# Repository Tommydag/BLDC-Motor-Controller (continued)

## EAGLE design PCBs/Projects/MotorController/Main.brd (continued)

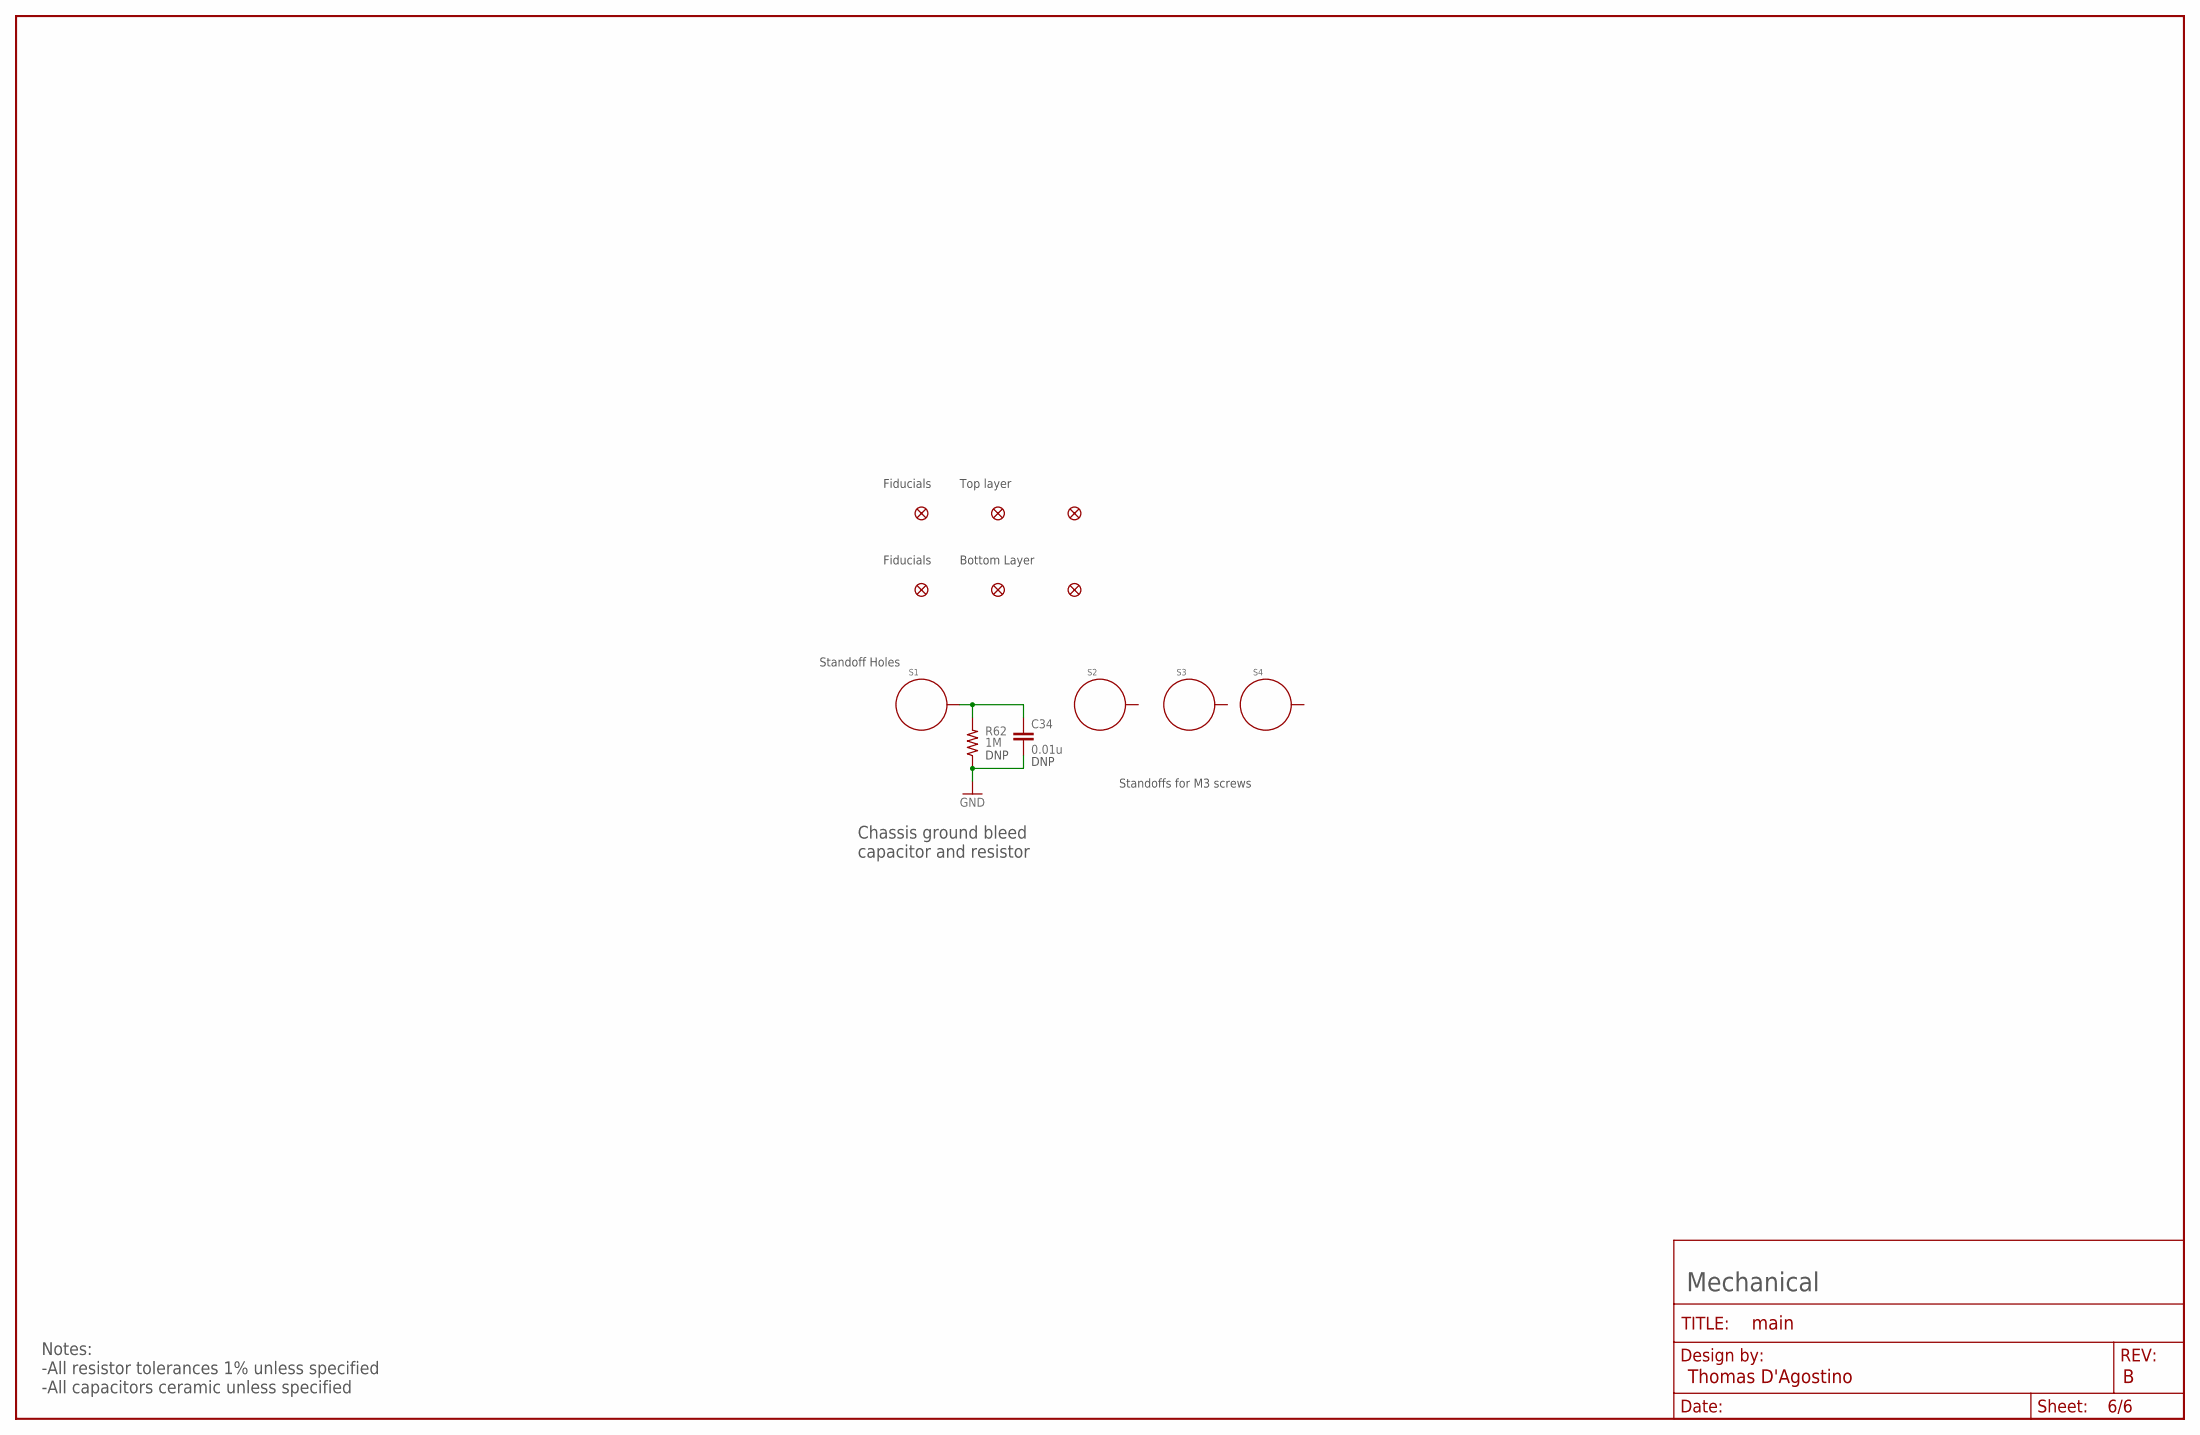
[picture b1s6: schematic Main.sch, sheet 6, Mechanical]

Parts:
C34: 0.01u; 0805
FD1, FD2, FD3, FD4, FD5, FD6: FIDUCIAL1X2; FIDUCIAL-1X2
FRAME6: FRAME-LEDGER; CREATIVE_COMMONS
R62: 1M; 1206
S1, S2, S3, S4: STANDOFF_ELECTRICAL; STANDOFF-ELECTRICAL

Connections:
GND: C34.2, R62.1; also elsewhere on the board
unnamed: C34.1, R62.2, S1.P1

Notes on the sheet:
Fiducials
Standoff Holes
Top layer
Standoffs for M3 screws
Mechanical
Chassis ground bleed capacitor and resistor
Notes: -All resistor tolerances 1% unless specified -All capacitors ceramic unless specified
Bottom Layer
DNP

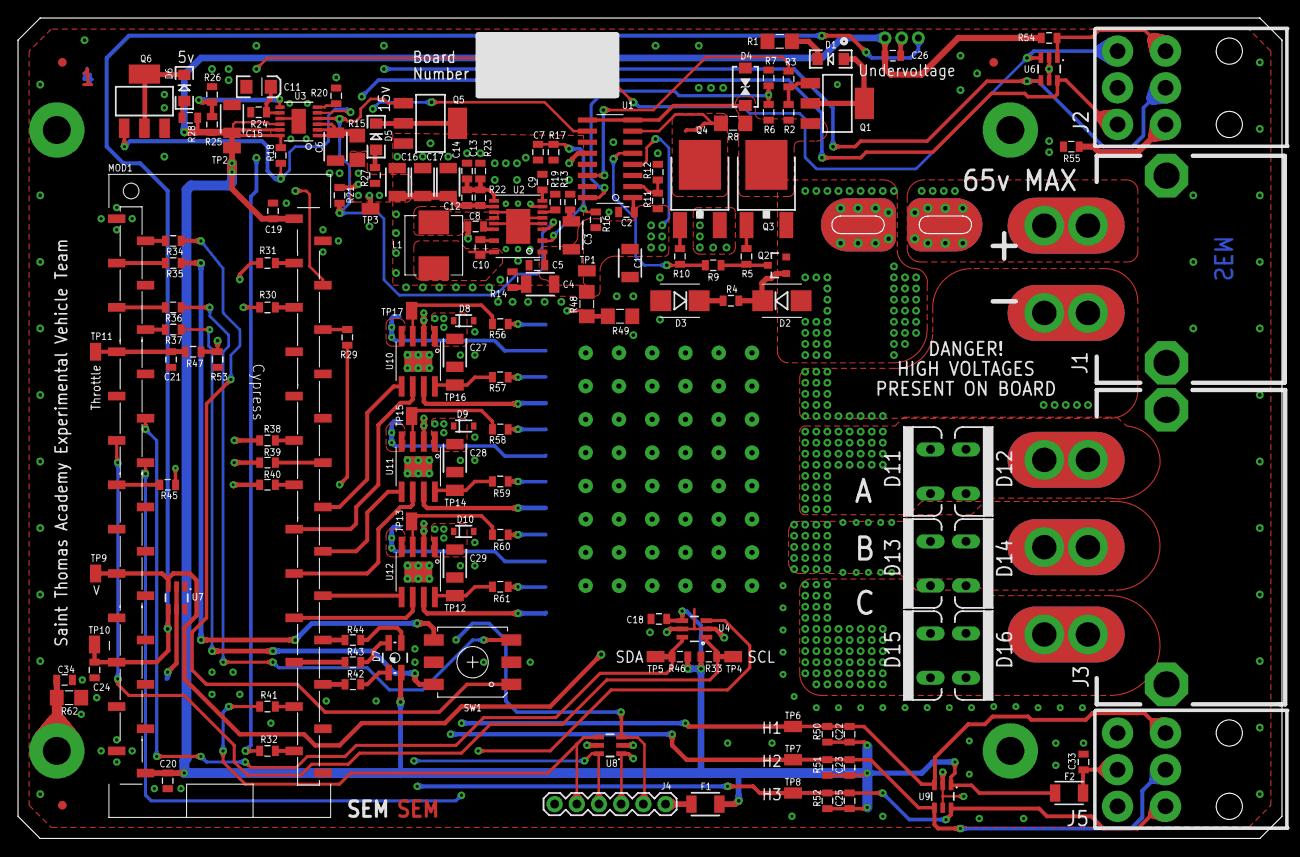
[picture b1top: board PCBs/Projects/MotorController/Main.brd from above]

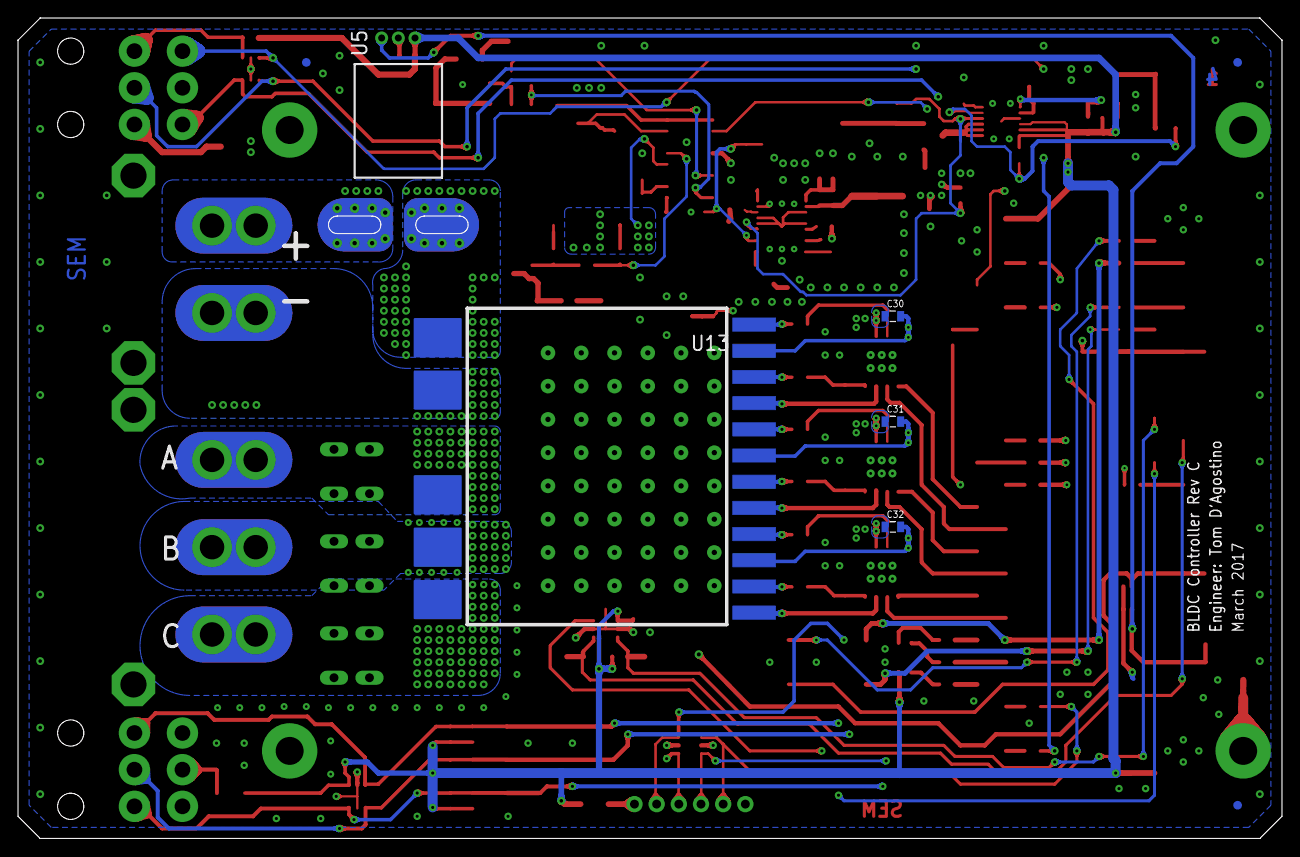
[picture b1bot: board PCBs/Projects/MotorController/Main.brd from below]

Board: 4 copper layers, 144.8 x 94.0 mm, 174 parts (8 on the bottom side), 110 nets.

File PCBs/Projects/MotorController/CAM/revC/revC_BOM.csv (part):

"Part";"Value";"Device";"Package";"Description";"PROD_ID";"VALUE";
"C1";"4.7u";"CAP1210";"1210";"Capacitor";"";"";
"C2";"47n";"CAP0805";"0805";"Capacitor";"";"";
"C3";"4.7u";"CAP1210";"1210";"Capacitor";"";"";
"C4";"2.2u";"CAP1210";"1210";"Capacitor";"";"";
"C5";"0.1u";"CAP0805";"0805";"Capacitor";"";"";
"C6";"10u";"CAP1210";"1210";"Capacitor";"";"";
"C7";"0.01u";"CAP0805";"0805";"Capacitor";"";"";
"C8";"2.2u";"CAP0805";"0805";"Capacitor";"";"";
"C9";"5600p";"CAP0805";"0805";"Capacitor";"";"";
"C10";"0.1u";"CAP0805";"0805";"Capacitor";"";"";
"C11";"4.7";"CAP_POL1206";"EIA3216";"Capacitor Polarized";"";"";
"C12";"200p";"CAP0805";"0805";"Capacitor";"";"";
"C13";"DNP";"CAP0805";"0805";"Capacitor";"";"";
"C14";"47u";"CAP1210";"1210";"Capacitor";"";"";
"C15";"10u";"CAP1210";"1210";"Capacitor";"";"";
"C16";"47u";"CAP1210";"1210";"Capacitor";"";"";
"C17";"47u";"CAP1210";"1210";"Capacitor";"";"";
"C18";"0.1u";"CAP0805";"0805";"Capacitor";"";"";
"C19";"0.1u";"CAP0805";"0805";"Capacitor";"";"";
"C20";"0.1u";"CAP0805";"0805";"Capacitor";"";"";
"C21";"0.1u";"CAP0805";"0805";"Capacitor";"";"";
"C22";"0.01u";"CAP0805";"0805";"Capacitor";"";"";
"C23";"0.01u";"CAP0805";"0805";"Capacitor";"";"";
"C24";"0.01u";"CAP0805";"0805";"Capacitor";"";"";
"C25";"0.01u";"CAP0805";"0805";"Capacitor";"";"";
"C26";"0.1u";"CAP0805";"0805";"Capacitor";"";"";
"C27";"4.7u";"CAP1210";"1210";"Capacitor";"";"";
"C28";"4.7u";"CAP1210";"1210";"Capacitor";"";"";
"C29";"4.7u";"CAP1210";"1210";"Capacitor";"";"";
"C30";"0.1u";"CAP0805";"0805";"Capacitor";"";"";
"C31";"0.1u";"CAP0805";"0805";"Capacitor";"";"";
"C32";"0.1u";"CAP0805";"0805";"Capacitor";"";"";
"C33";"0.1u";"CAP0805";"0805";"Capacitor";"";"";
"C34";"0.01u";"CAP0805";"0805";"Capacitor";"";"";
"D1";"RED";"LED-RED1206";"LED-1206";"Assorted Red LEDs";"DIO-09912";"RED";
"D2";"S3BB";"DIODES3BB";"SMB-DIODE";"Diode";"";"";
"D3";"S3BB";"DIODES3BB";"SMB-DIODE";"Diode";"";"";
"D4";"SMAJ70CA";"SMAJ70CABIDIRECTIONAL";"SMA-DIODE-BI";"The SMAJ series is designed specifically to protect";"";"";
"D5";"GREEN";"LED-RED1206";"LED-1206";"Assorted Red LEDs";"DIO-09912";"RED";
"D6";"GREEN";"LED-RED1206";"LED-1206";"Assorted Red LEDs";"DIO-09912";"RED";
"D7";"CLV1A-FKB";"0.13_RGB_LEDCLV1A-FKB";"P-LCC-4-3";"Everlight Red/Green/Blue LED";"";"";
"D8";"SZMM3Z18VST1G";"DIODE-ZENERSZMM3Z18VST1G";"SOD-323";"Zener Diode";"";"";
"D9";"SZMM3Z18VST1G";"DIODE-ZENERSZMM3Z18VST1G";"SOD-323";"Zener Diode";"";"";
"D10";"SZMM3Z18VST1G";"DIODE-ZENERSZMM3Z18VST1G";"SOD-323";"Zener Diode";"";"";
"D11";"MBRF10H100";"DIODE-SCHOTTKY-MBRF1090_V";"TO220V_2";"Schottky diodes in SFE's production catalog";"";"";
"D12";"MBRF10H100";"DIODE-SCHOTTKY-MBRF1090_V";"TO220V_2";"Schottky diodes in SFE's production catalog";"";"";
"D13";"MBRF10H100";"DIODE-SCHOTTKY-MBRF1090_V";"TO220V_2";"Schottky diodes in SFE's production catalog";"";"";
"D14";"MBRF10H100";"DIODE-SCHOTTKY-MBRF1090_V";"TO220V_2";"Schottky diodes in SFE's production catalog";"";"";
"D15";"MBRF10H100";"DIODE-SCHOTTKY-MBRF1090_V";"TO220V_2";"Schottky diodes in SFE's production catalog";"";"";
"D16";"MBRF10H100";"DIODE-SCHOTTKY-MBRF1090_V";"TO220V_2";"Schottky diodes in SFE's production catalog";"";"";
"F1";"B59607A120A62";"PTC1210";"1210";"Resettable Fuse PTC";"";"";
"F2";"B59607A120A62";"PTC1210";"1210";"Resettable Fuse PTC";"";"";
"FD1";"FIDUCIAL1X2";"FIDUCIAL1X2";"FIDUCIAL-1X2";"Fiducial Alignment Points";"";"";
"FD2";"FIDUCIAL1X2";"FIDUCIAL1X2";"FIDUCIAL-1X2";"Fiducial Alignment Points";"";"";
"FD3";"FIDUCIAL1X2";"FIDUCIAL1X2";"FIDUCIAL-1X2";"Fiducial Alignment Points";"";"";
"FD4";"FIDUCIAL1X2";"FIDUCIAL1X2";"FIDUCIAL-1X2";"Fiducial Alignment Points";"";"";
"FD5";"FIDUCIAL1X2";"FIDUCIAL1X2";"FIDUCIAL-1X2";"Fiducial Alignment Points";"";"";
"FD6";"FIDUCIAL1X2";"FIDUCIAL1X2";"FIDUCIAL-1X2";"Fiducial Alignment Points";"";"";
"FRAME1";"FRAME-LEDGER";"FRAME-LEDGER";"CREATIVE_COMMONS";"Schematic Frame";"";"";
"FRAME2";"FRAME-LEDGER";"FRAME-LEDGER";"CREATIVE_COMMONS";"Schematic Frame";"";"";
"FRAME3";"FRAME-LEDGER";"FRAME-LEDGER";"CREATIVE_COMMONS";"Schematic Frame";"";"";
"FRAME4";"FRAME-LEDGER";"FRAME-LEDGER";"CREATIVE_COMMONS";"Schematic Frame";"";"";
"FRAME5";"FRAME-LEDGER";"FRAME-LEDGER";"CREATIVE_COMMONS";"Schematic Frame";"";"";
"FRAME6";"FRAME-LEDGER";"FRAME-LEDGER";"CREATIVE_COMMONS";"Schematic Frame";"";"";
"J1";"";"M02MINIFIT-SR";"MINIFIT_SR";"Standard 2-pin 0.1" header. Use with";"";"";
"J2";"";"M03X2MINIFIT_JR";"2X03_MINIFIT_JR";"2x3 .1" header.";"";"";
"J3";"";"M03MINIFIT-SR3";"MINIFIT-SRX3";"Header 3";"";"";
"J4";"";"M06SILK_FEMALE_PTH";"1X06";"Header 6";"CONN-08437";"";
"J5";"";"M03X2MINIFIT_JR";"2X03_MINIFIT_JR";"2x3 .1" header.";"";"";
"L1";"22u";"INDUCTORSRP7050TA-220M";"IND_SMD_SRP7050TA";"Inductors";"";"";
"MOD1";"PSOC5LP-DEVBRDCY8CKIT-059";"PSOC5LP-DEVBRDCY8CKIT-059";"CYKIT059";"";"";"";
"Q1";"ZXMP10A17GQ";"MOSFET-PCHANNELZXMP10A17GQ";"SOT223";"Generic PMOSFET";"";"";
"Q2";"MMBT5551LT1G";"TRANSISTOR_NPNMMBT5551LT1G";"SOT23-3";"Generic NPN BJT";"";"";
"Q3";"BUK9240-100A.118";"MOSFET-NCHANNELBUK9240-100A.118";"DPAK";"Common NMOSFET Parts";"";"";
"Q4";"BUK9240-100A.118";"MOSFET-NCHANNELBUK9240-100A.118";"DPAK";"Common NMOSFET Parts";"";"";
"Q5";"NCV8440";"MOSFET-NCHANNELNCV8440";"SOT223";"Common NMOSFET Parts";"";"";
"Q6";"NCV8440";"MOSFET-NCHANNELNCV8440";"SOT223";"Common NMOSFET Parts";"";"";
"R1";"2.8k";"RESISTOR1206";"1206";"Resistor";"";"";
"R2";"47k";"RESISTOR0805-RES";"0805";"Resistor";"";"";
"R3";"100";"RESISTOR0805-RES";"0805";"Resistor";"";"";
"R4";"10k";"RESISTOR0805-RES";"0805";"Resistor";"";"";
"R5";"10";"RESISTOR0805-RES";"0805";"Resistor";"";"";
"R6";"124k";"RESISTOR0805-RES";"0805";"Resistor";"";"";
"R7";"10k";"RESISTOR0805-RES";"0805";"Resistor";"";"";
"R8";"0.2";"RESISTOR1206";"1206";"Resistor";"";"";
"R9";"1M";"RESISTOR0805-RES";"0805";"Resistor";"";"";
"R10";"10";"RESISTOR0805-RES";"0805";"Resistor";"";"";
"R11";"274k";"RESISTOR0805-RES";"0805";"Resistor";"";"";
"R12";"4.99k";"RESISTOR0805-RES";"0805";"Resistor";"";"";
"R13";"10";"RESISTOR0805-RES";"0805";"Resistor";"";"";
"R14";"0.5";"RESISTOR0805-RES";"0805";"Resistor";"";"";
"R15";"2";"RESISTOR1206";"1206";"Resistor";"";"";
"R16";"124k";"RESISTOR0805-RES";"0805";"Resistor";"";"";
"R17";"10k";"RESISTOR0805-RES";"0805";"Resistor";"";"";
"R18";"47k";"RESISTOR0805-RES";"0805";"Resistor";"";"";
"R19";"25.5k";"RESISTOR0805-RES";"0805";"Resistor";"";"";
"R20";"499";"RESISTOR0805-RES";"0805";"Resistor";"";"";
"R21";"47k";"RESISTOR0805-RES";"0805";"Resistor";"";"";
"R22";"1M";"RESISTOR0805-RES";"0805";"Resistor";"";"";
"R23";"57.6k";"RESISTOR0805-RES";"0805";"Resistor";"";"";
"R24";"49.9k";"RESISTOR0805-RES";"0805";"Resistor";"";"";
"R25";"140k";"RESISTOR0805-RES";"0805";"Resistor";"";"";
"R26";"10k";"RESISTOR0805-RES";"0805";"Resistor";"";"";
"R27";"2.7k";"RESISTOR0805-RES";"0805";"Resistor";"";"";
"R28";"1k";"RESISTOR0805-RES";"0805";"Resistor";"";"";
"R29";"100";"RESISTOR0805-RES";"0805";"Resistor";"";"";
"R30";"100";"RESISTOR0805-RES";"0805";"Resistor";"";"";
"R31";"100";"RESISTOR0805-RES";"0805";"Resistor";"";"";
"R32";"100";"RESISTOR0805-RES";"0805";"Resistor";"";"";
"R33";"4.7k";"RESISTOR0805-RES";"0805";"Resistor";"";"";
"R34";"100";"RESISTOR0805-RES";"0805";"Resistor";"";"";
"R35";"100";"RESISTOR0805-RES";"0805";"Resistor";"";"";
"R36";"100";"RESISTOR0805-RES";"0805";"Resistor";"";"";
"R37";"100";"RESISTOR0805-RES";"0805";"Resistor";"";"";
"R38";"100";"RESISTOR0805-RES";"0805";"Resistor";"";"";
"R39";"100";"RESISTOR0805-RES";"0805";"Resistor";"";"";
"R40";"100";"RESISTOR0805-RES";"0805";"Resistor";"";"";
"R41";"100";"RESISTOR0805-RES";"0805";"Resistor";"";"";
"R42";"1k";"RESISTOR0805-RES";"0805";"Resistor";"";"";
"R43";"1k";"RESISTOR0805-RES";"0805";"Resistor";"";"";
"R44";"1k";"RESISTOR0805-RES";"0805";"Resistor";"";"";
"R45";"100";"RESISTOR0805-RES";"0805";"Resistor";"";"";
"R46";"4.7k";"RESISTOR0805-RES";"0805";"Resistor";"";"";
"R47";"100";"RESISTOR0805-RES";"0805";"Resistor";"";"";
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
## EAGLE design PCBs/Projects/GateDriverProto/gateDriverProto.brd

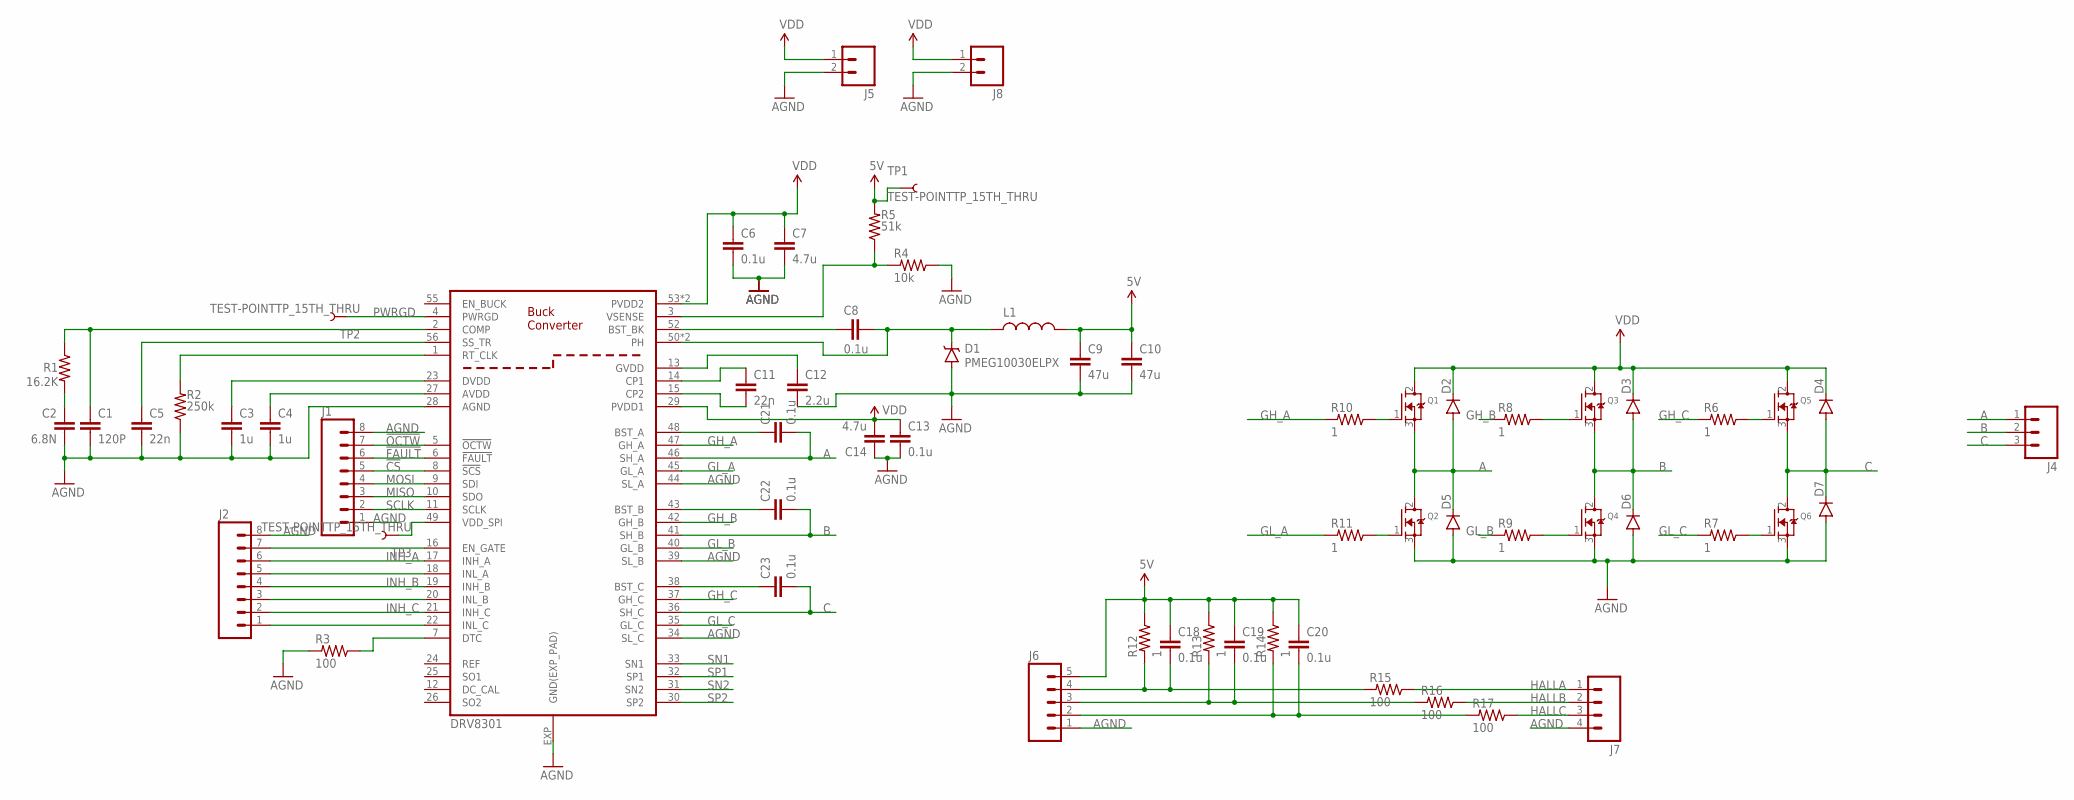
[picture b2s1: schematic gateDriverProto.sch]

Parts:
C1: 120P; 0805
C2: 6.8N; 0805
C3, C4: 1u; 0805
C5, C11: 22n; 0805
C6, C8, C13, C18, C19, C20: 0.1u; 0805
C7, C14: 4.7u; 1210
C9, C10: 47u; 1210
C12: 2.2u; 1210
C21, C22, C23: 0.1u; CAP-PTH-SMALL
D1: PMEG10030ELPX; SMB-DIODE
D2, D3, D4, D5, D6, D7: DIODEPTH; DIODE-1N4001
J1, J2: M08; 1X08_ROUND
J4: M03LONGPADS; 1X03_LONGPADS
J5, J8: M02LOCK_LONGPADS; 1X02_LOCK_LONGPADS
J6: M05PTH_LONGPADS; 1X05_LONGPADS
J7: M04PTH; 1X04
L1: INDUCTORPWR; CDRH125
Q1, Q2, Q3, Q4, Q5, Q6: MOSFET-NGDS_TO220V; TO220V
R1: 16.2K; AXIAL-0.1
R2: 250k; AXIAL-0.1
R3, R15, R16, R17: 100; AXIAL-0.1
R4: 10k; AXIAL-0.1
R5: 51k; AXIAL-0.1
R6, R7, R8, R9, R10, R11, R12, R13, R14: 1; AXIAL-0.1
TP1, TP2, TP3: TEST-POINTTP_15TH_THRU; TP_15TH
U1: DRV8301; HTSSOP_56

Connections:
5V: C9.1, C10.1, C18.1, C19.1, C20.1, J6.5, L1.2, R5.P$2 (2), R12.P$1 (1), R13.P$1 (1), R14.P$1 (1), TP1.P$1
!CS: J1.5, U1.8 (!SCS)
!FAULT: J1.6, U1.6 (!FAULT)
!OCTW: J1.7, U1.5 (!OCTW)
A: C21.2, D2.A, D5.C, J4.1, Q1.3 (S), Q2.2 (D), U1.46 (SH_A)
AGND: C1.2, C2.2, C3.2, C4.2, C5.2, C6.2, C7.2, C9.2, C10.2, C12.2, C13.2, C14.1, D1.A, D5.A, D6.A, D7.A, J1.1, J1.8, J2.8, J5.2, J6.1, J7.4, J8.2, Q2.3 (S), Q4.3 (S), Q6.3 (S), R2.P$1 (1), R3.P$2 (2), R4.P$1 (1), U1.28 (AGND), U1.34 (SL_C), U1.39 (SL_B), U1.44 (SL_A), U1.EXP (GND(EXP_PAD))
B: C22.2, D3.A, D6.C, J4.2, Q3.3 (S), Q4.2 (D), U1.41 (SH_B)
C: C23.2, D4.A, D7.C, J4.3, Q5.3 (S), Q6.2 (D), U1.36 (SH_C)
GH_A: R10.P$2 (2), U1.47 (GH_A)
GH_B: R8.P$2 (2), U1.42 (GH_B)
GH_C: R6.P$2 (2), U1.37 (GH_C)
GL_A: R11.P$2 (2), U1.45 (GL_A)
GL_B: R9.P$2 (2), U1.40 (GL_B)
GL_C: R7.P$2 (2), U1.35 (GL_C)
HALLA: J7.1, R15.P$1 (1)
HALLB: J7.2, R16.P$1 (1)
HALLC: J7.3, R17.P$1 (1)
INH_A: J2.6, U1.17 (INH_A)
INH_B: J2.4, U1.19 (INH_B)
INH_C: J2.2, U1.21 (INH_C)
MISO: J1.3, U1.10 (SDO)
MOSI: J1.4, U1.9 (SDI)
unnamed: R2.P$2 (2), U1.1 (RT_CLK)
unnamed: C2.1, R1.P$2 (2)
unnamed: C5.1, U1.56 (SS_TR)
unnamed: J2.7, U1.16 (EN_GATE)
unnamed: C3.1, U1.23 (DVDD)
unnamed: C1.1, R1.P$1 (1), U1.2 (COMP)
unnamed: C4.1, U1.27 (AVDD)
unnamed: R3.P$1 (1), U1.7 (DTC)
unnamed: R4.P$2 (2), R5.P$1 (1), U1.3 (VSENSE)
unnamed: C8.1, U1.52 (BST_BK)
unnamed: C8.2, D1.C, L1.1, U1.50 (PH), U1.51 (PH)
unnamed: C12.1, U1.13 (GVDD)
unnamed: C22.1, U1.43 (BST_B)
unnamed: C21.1, U1.48 (BST_A)
unnamed: C18.2, J6.4, R12.P$2 (2), R15.P$2 (2)
unnamed: C11.2, U1.15 (CP2)
unnamed: C11.1, U1.14 (CP1)
unnamed: TP3.P$1, U1.49 (VDD_SPI)
unnamed: C19.2, J6.3, R13.P$2 (2), R16.P$2 (2)
unnamed: C23.1, U1.38 (BST_C)
unnamed: C20.2, J6.2, R14.P$2 (2), R17.P$2 (2)
unnamed: Q5.1 (G), R6.P$1 (1)
unnamed: J2.5, U1.18 (INL_A)
unnamed: Q6.1 (G), R7.P$1 (1)
unnamed: J2.1, U1.22 (INL_C)
unnamed: Q3.1 (G), R8.P$1 (1)
unnamed: Q4.1 (G), R9.P$1 (1)
unnamed: Q2.1 (G), R11.P$1 (1)
unnamed: Q1.1 (G), R10.P$1 (1)
unnamed: J2.3, U1.20 (INL_B)
PWRGD: TP2.P$1, U1.4 (PWRGD)
SCLK: J1.2, U1.11 (SCLK)
SN1: U1.33 (SN1)
SN2: U1.31 (SN2)
SP1: U1.32 (SP1)
SP2: U1.30 (SP2)
VDD: C6.1, C7.1, C13.1, C14.2, D2.C, D3.C, D4.C, J5.1, J8.1, Q1.2 (D), Q3.2 (D), Q5.2 (D), U1.29 (PVDD1), U1.53 (PVDD2), U1.54 (PVDD2)

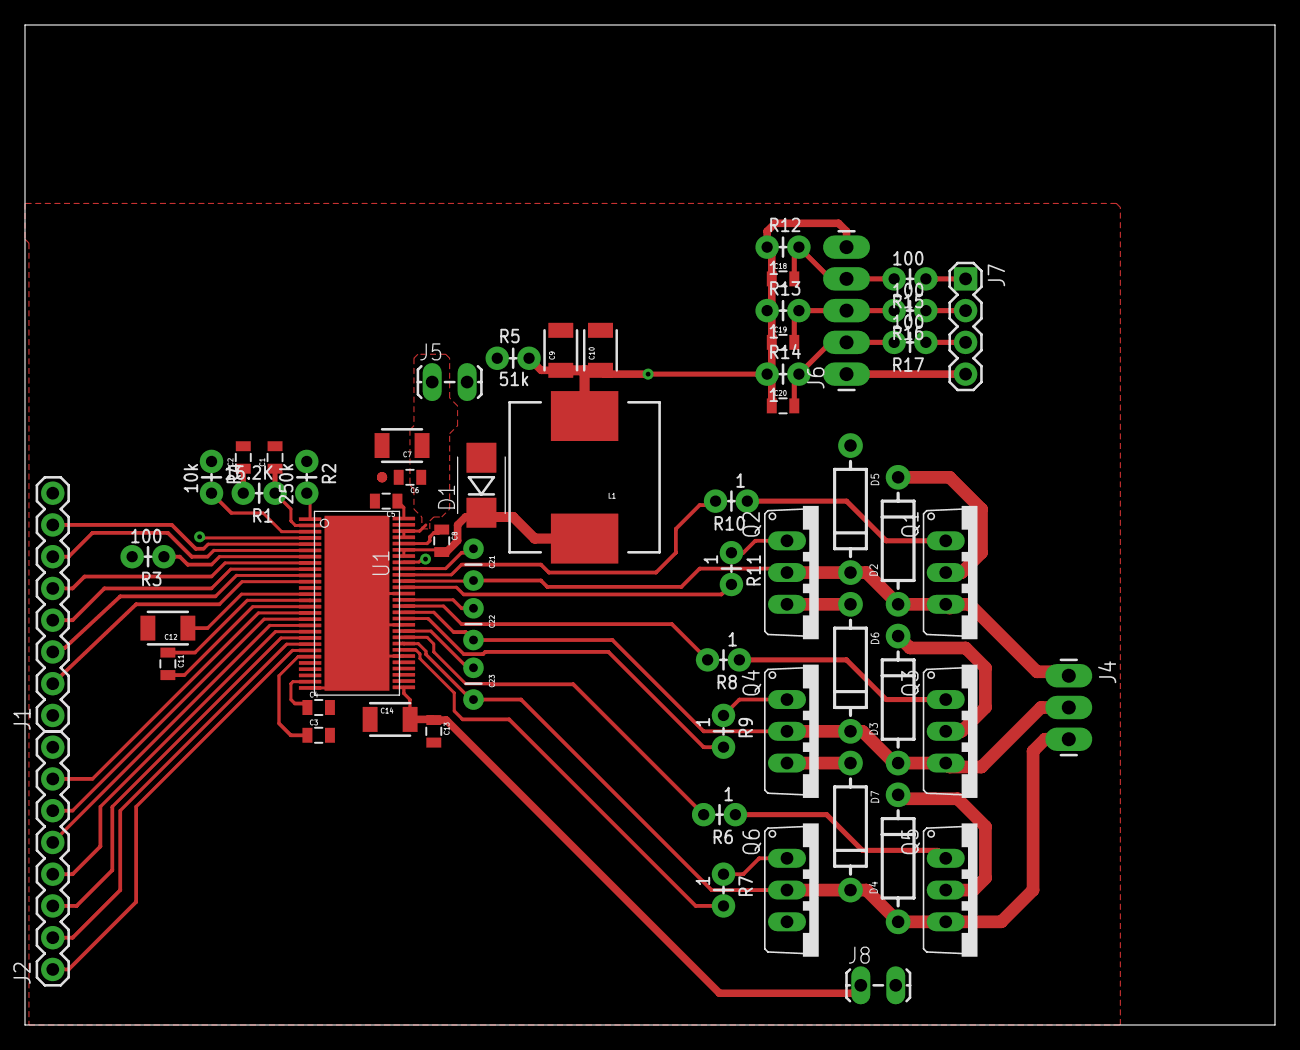
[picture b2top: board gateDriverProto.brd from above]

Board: 1 copper layer, 100.0 x 80.0 mm, 62 parts (0 on the bottom side), 55 nets.

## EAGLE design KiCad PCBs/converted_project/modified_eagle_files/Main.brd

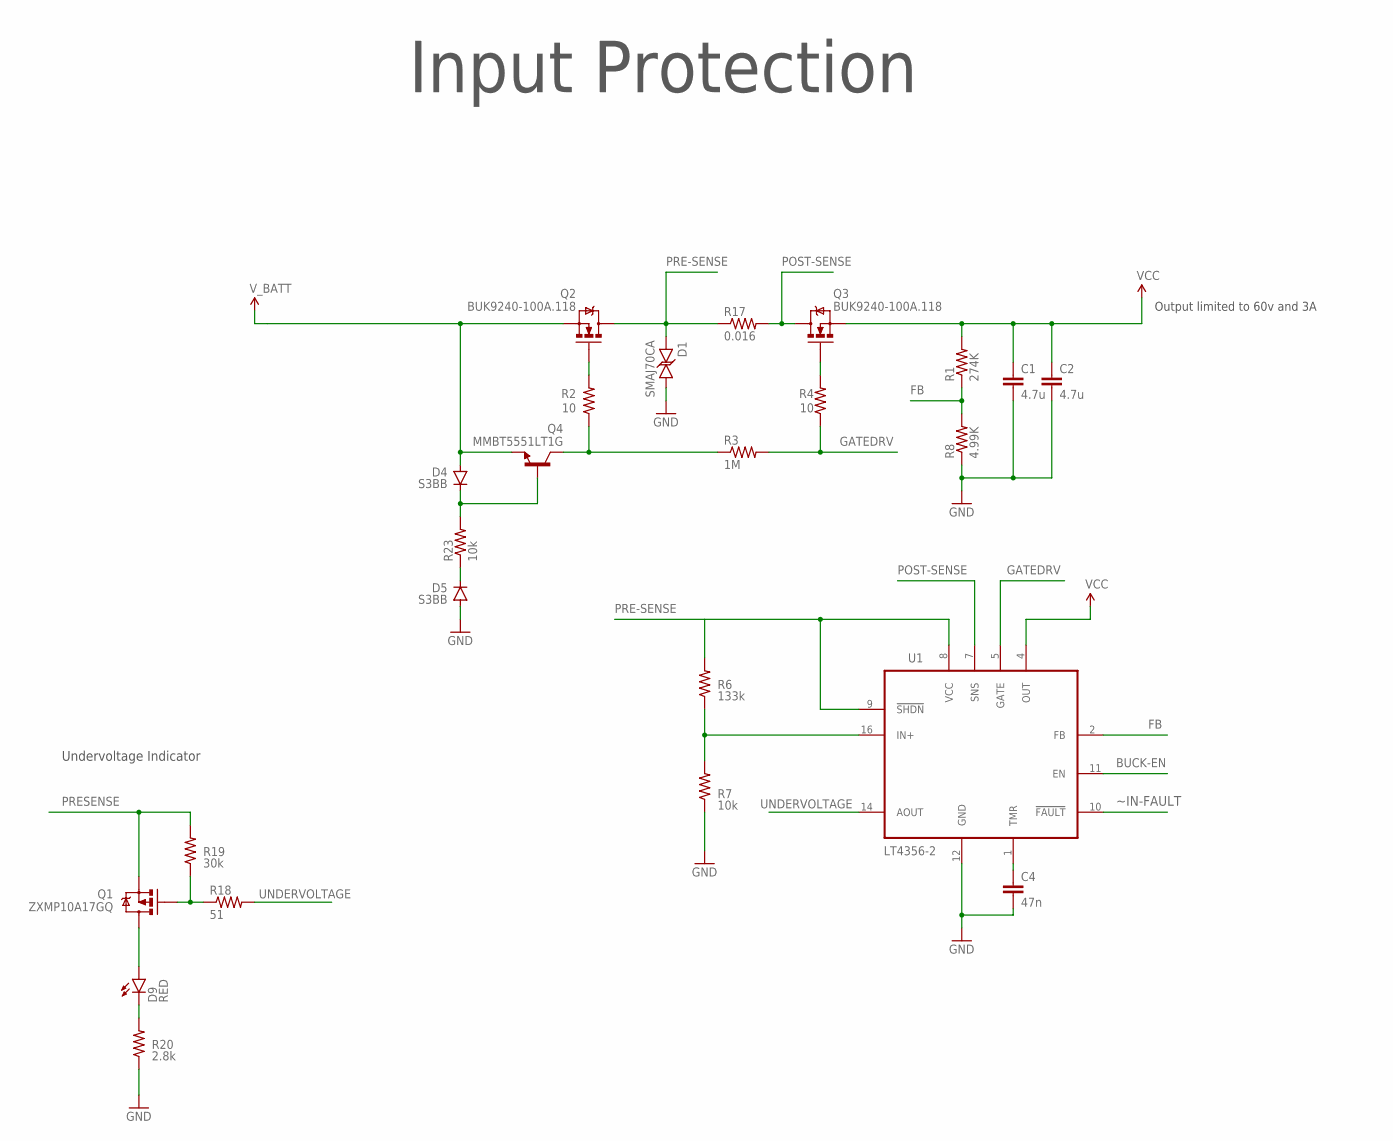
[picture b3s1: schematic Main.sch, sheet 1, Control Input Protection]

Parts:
C1, C2: 4.7u; 1210
C4: 47n; 0805
D1: SMAJ70CA; SMA-DIODE
D4, D5: S3BB; SMB-DIODE
D9: RED; LED-1206
Q1: ZXMP10A17GQ; SOT223
Q2, Q3: BUK9240-100A.118; DPAK
Q4: MMBT5551LT1G; SOT23-3
R1: 274K; 1206
R2: 10; 1206
R3: 1M; 0805
R4: 10; 0805
R6: 133k; 0805
R7: 10k; 0805
R8: 4.99K; 1206
R17: 0.016; R2010
R18: 51; 1206
R19: 30k; 1206
R20: 2.8k; 1206
R23: 10k; 1206
U1: LT4356-2; SOIC-16

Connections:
BUCK-EN: U1.11 (EN); also elsewhere on the board
FB: R1.1, R8.2, U1.2 (FB)
GATEDRV: R3.2, R4.1, U1.5 (GATE)
GND: C1.2, C2.2, C4.2, D1.C, D5.A, R7.1, R8.1, R20.1, U1.12 (GND); also elsewhere on the board
unnamed: C4.1, U1.1 (TMR)
unnamed: D9.C, R20.2
unnamed: Q2.1 (G), R2.2
unnamed: D4.A, Q2.3 (S), Q4.2 (E)
unnamed: D4.C, Q4.1 (B), R23.2
unnamed: Q3.1 (G), R4.2
unnamed: R6.1, R7.2, U1.16 (IN+)
unnamed: Q1.1 (G), R18.1, R19.1
unnamed: Q4.3 (C), R2.1, R3.1
unnamed: D9.A, Q1.2 (D), Q1.4 (D)
unnamed: D5.C, R23.1
POST-SENSE: Q3.4 (D), R17.2, U1.7 (SNS)
PRE-SENSE: D1.A, Q2.4 (D), R6.2, R17.1, U1.8 (VCC), U1.9 (!SHDN)
PRESENSE: Q1.3 (S), R19.2
UNDERVOLTAGE: R18.2, U1.14 (AOUT)
VCC: C1.1, C2.1, Q3.3 (S), R1.2, U1.4 (OUT); also elsewhere on the board
~IN-FAULT: U1.10 (!FAULT)

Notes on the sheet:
Output limited to 60v and 3A
Input Protection
Undervoltage Indicator

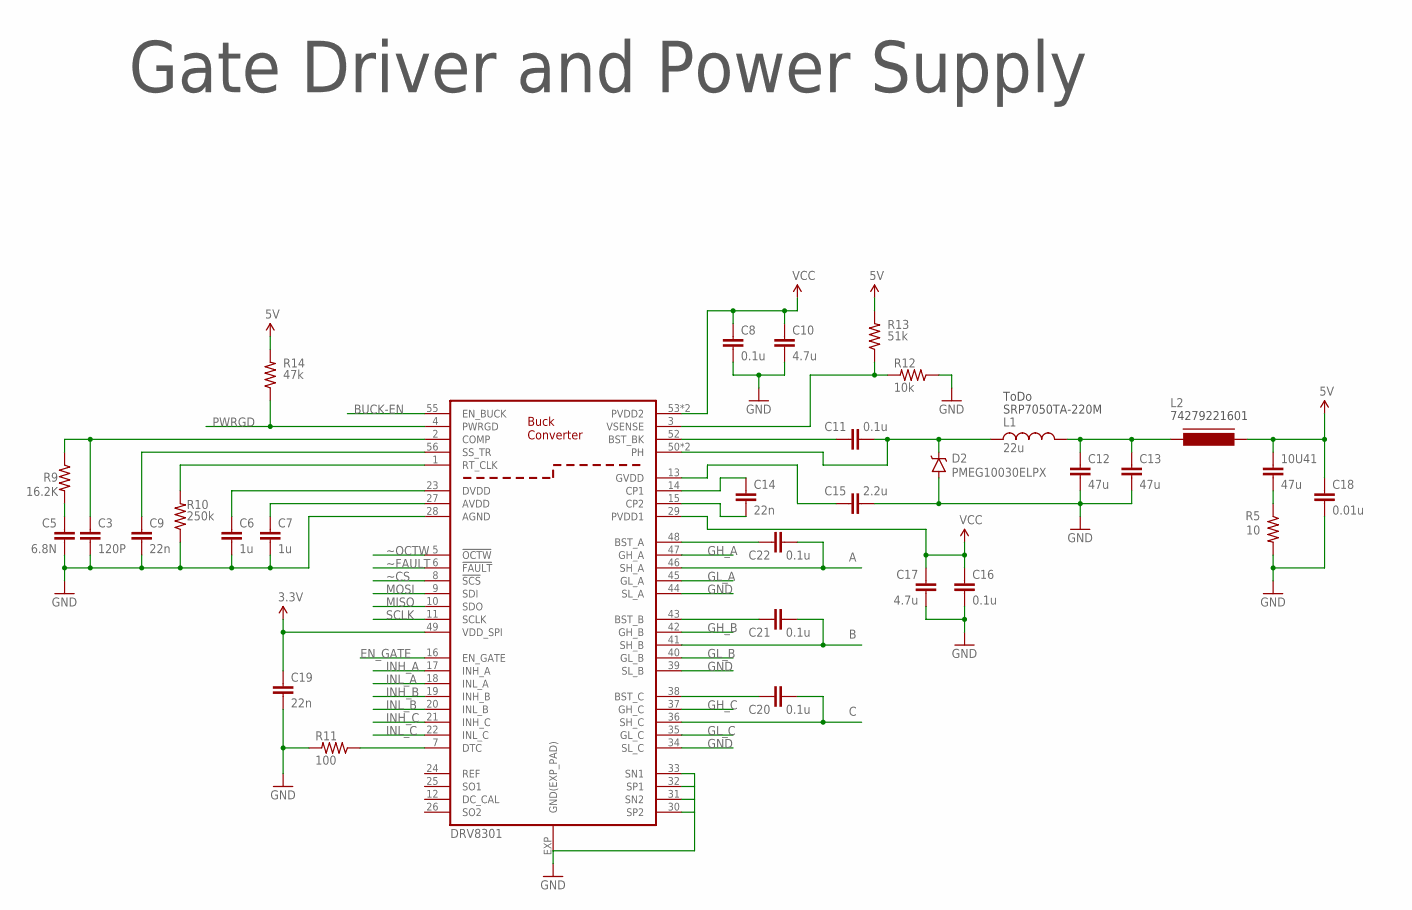
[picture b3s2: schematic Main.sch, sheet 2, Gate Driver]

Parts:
10U41: 47u; 1210
C3: 120P; 0805
C5: 6.8N; 0805
C6, C7: 1u; 0805
C8, C11, C16, C20, C21, C22: 0.1u; 0805
C9, C14, C19: 22n; 0805
C10, C17: 4.7u; 1210
C12, C13: 47u; 1210
C15: 2.2u; 1210
C18: 0.01u; 0805
D2: PMEG10030ELPX; SMB-DIODE
L1: 22u; CDRH125
L2: FERRITE-1206; FB1206
R5: 10; 0805
R9: 16.2K; 0805
R10: 250k; 0805
R11: 100; 0805
R12: 10k; 0805
R13: 51k; 0805
R14: 47k; 0805
U2: DRV8301; HTSSOP_56

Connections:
3.3V: C19.1, U2.49 (VDD_SPI)
5V: 10U41.1, C18.1, L2.1, R13.2, R14.2; also elsewhere on the board
A: C22.2, U2.46 (SH_A); also elsewhere on the board
B: C21.2, U2.41 (SH_B); also elsewhere on the board
BUCK-EN: U2.55 (EN_BUCK); also elsewhere on the board
C: C20.2, U2.36 (SH_C); also elsewhere on the board
EN_GATE: U2.16 (EN_GATE); also elsewhere on the board
GH_A: U2.47 (GH_A); also elsewhere on the board
GH_B: U2.42 (GH_B); also elsewhere on the board
GH_C: U2.37 (GH_C); also elsewhere on the board
GL_A: U2.45 (GL_A); also elsewhere on the board
GL_B: U2.40 (GL_B); also elsewhere on the board
GL_C: U2.35 (GL_C); also elsewhere on the board
GND: C3.2, C5.2, C6.2, C7.2, C8.2, C9.2, C10.2, C12.2, C13.2, C15.2, C16.2, C17.1, C18.2, C19.2, D2.A, R5.2, R10.1, R11.2, R12.1, U2.28 (AGND), U2.30 (SP2), U2.31 (SN2), U2.32 (SP1), U2.33 (SN1), U2.34 (SL_C), U2.39 (SL_B), U2.44 (SL_A), U2.EXP (GND(EXP_PAD)); also elsewhere on the board
INH_A: U2.17 (INH_A)
INH_B: U2.19 (INH_B)
INH_C: U2.21 (INH_C)
INL_A: U2.18 (INL_A)
INL_B: U2.20 (INL_B)
INL_C: U2.22 (INL_C)
MISO: U2.10 (SDO)
MOSI: U2.9 (SDI)
unnamed: R10.2, U2.1 (RT_CLK)
unnamed: C5.1, R9.2
unnamed: C6.1, U2.23 (DVDD)
unnamed: C3.1, R9.1, U2.2 (COMP)
unnamed: C7.1, U2.27 (AVDD)
unnamed: C9.1, U2.56 (SS_TR)
unnamed: R12.2, R13.1, U2.3 (VSENSE)
unnamed: C11.1, U2.52 (BST_BK)
unnamed: C11.2, D2.C, L1.1, U2.50 (PH), U2.51 (PH)
unnamed: C14.2, U2.15 (CP2)
unnamed: C14.1, U2.14 (CP1)
unnamed: C15.1, U2.13 (GVDD)
unnamed: C22.1, U2.48 (BST_A)
unnamed: C20.1, U2.38 (BST_C)
unnamed: R11.1, U2.7 (DTC)
unnamed: C21.1, U2.43 (BST_B)
unnamed: C12.1, C13.1, L1.2, L2.2
unnamed: 10U41.2, R5.1
PWRGD: R14.1, U2.4 (PWRGD)
SCLK: U2.11 (SCLK)
VCC: C8.1, C10.1, C16.1, C17.2, U2.29 (PVDD1), U2.53 (PVDD2), U2.54 (PVDD2); also elsewhere on the board
~CS: U2.8 (!SCS)
~FAULT: U2.6 (!FAULT)
~OCTW: U2.5 (!OCTW)

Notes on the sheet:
Gate Driver and Power Supply
74279221601
SRP7050TA-220M
ToDo
